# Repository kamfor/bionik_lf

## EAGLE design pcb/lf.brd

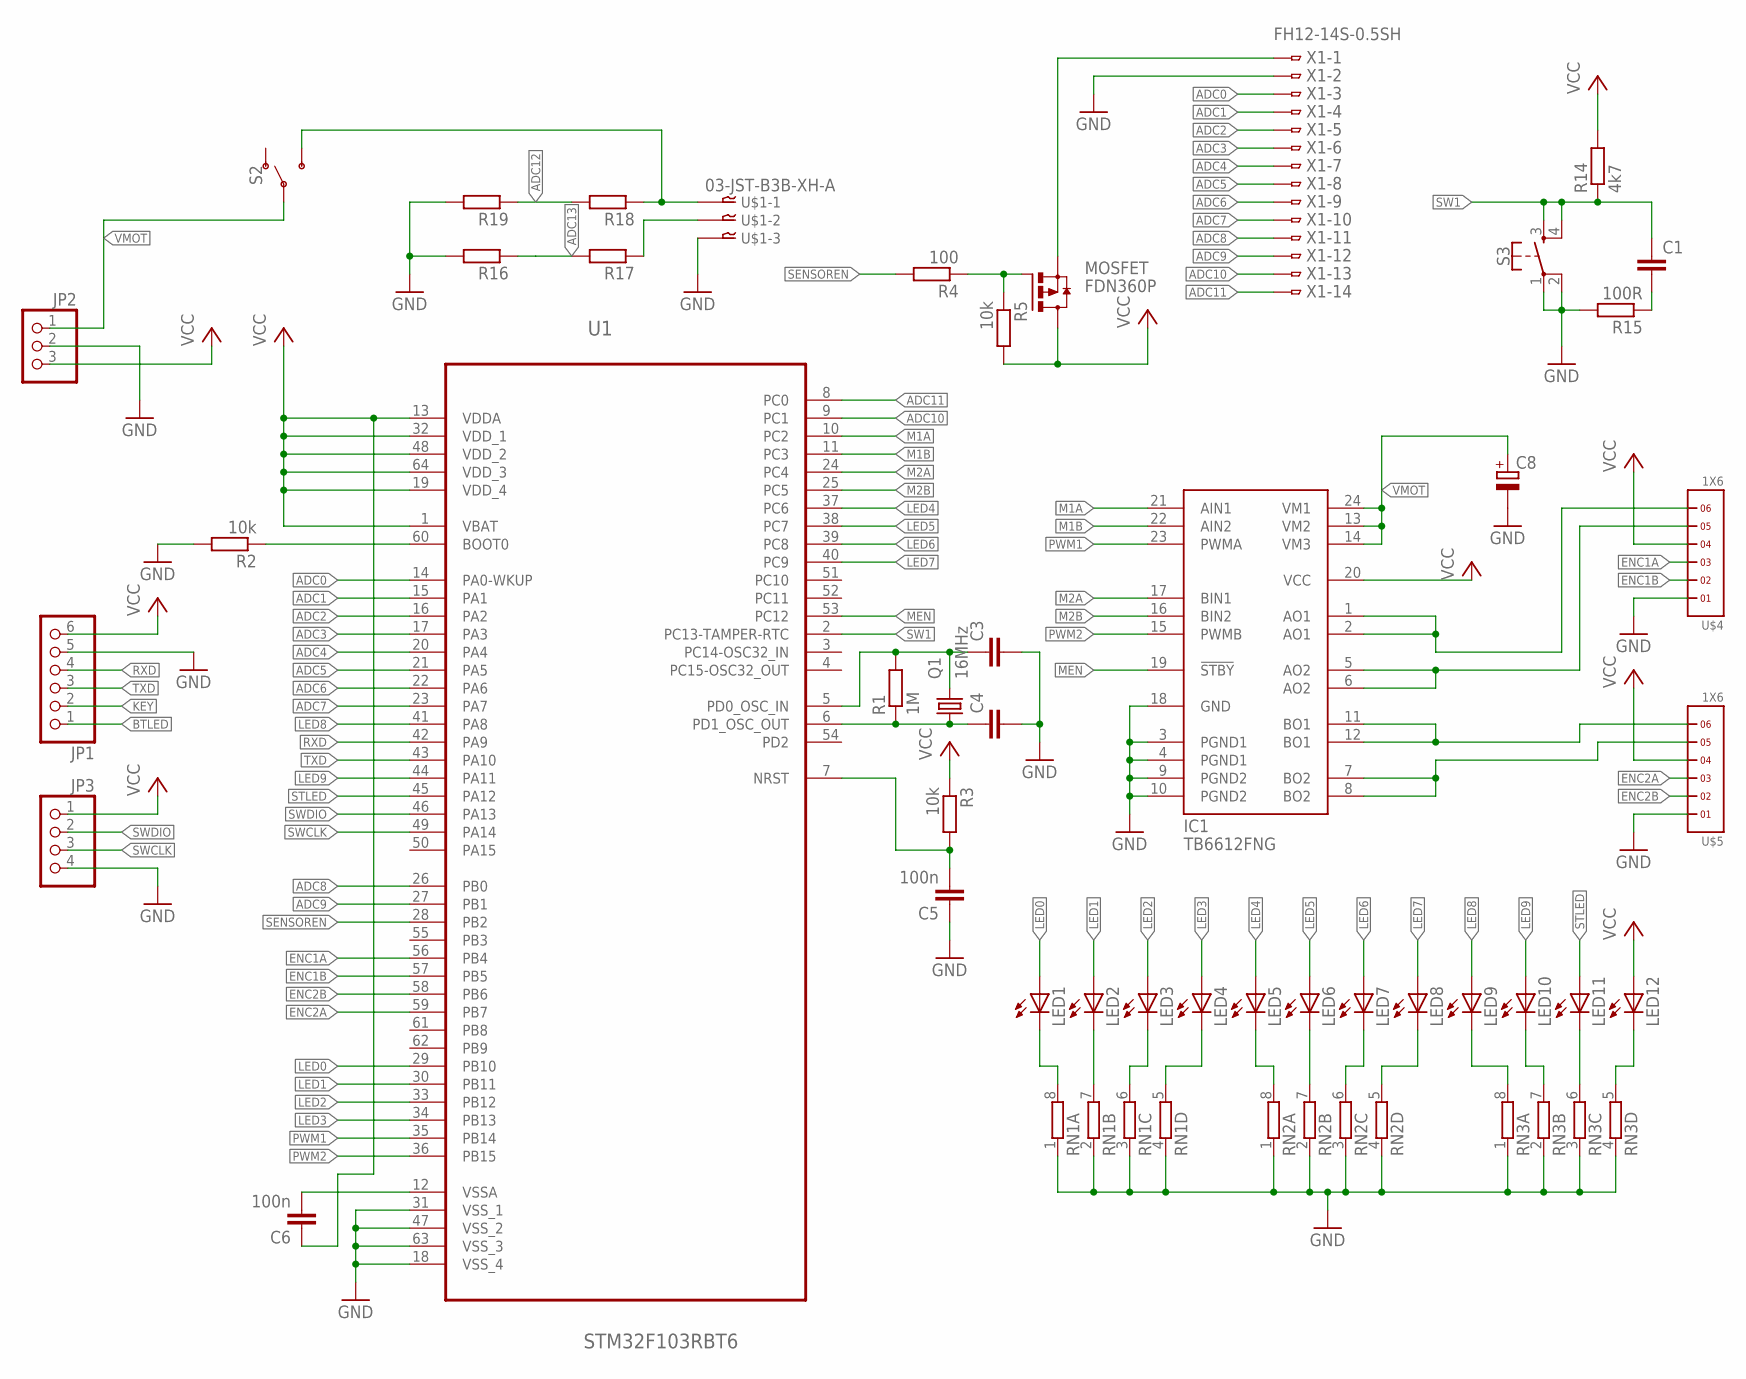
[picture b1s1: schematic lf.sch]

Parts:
C1, C3, C4: C-EUC0603K; C0603K
C5, C6: 100n; C0603K
C8: CPOL-EUC/6032-28R; C/6032-28R
IC1: TB6612FNG; SSOP24
JP1: PINHD-1X6; 1X06
JP2: PINHD-1X3; 1X03
JP3: PINHD-1X4; 1X04
LED1, LED2, LED3, LED4, LED5, LED6, LED7, LED8, LED9, LED10, LED11, LED12: LEDCHIPLED_0603; CHIPLED_0603
MOSFET: FDN360P; SUPER-SOT3
Q1: 16MHz; 3.2X2.5_KX-7
R1: 1M; R0603
R2, R3, R5: 10k; R0603
R4: 100; R0603
R14: 4k7; R0603
R15: 100R; R0603
R16, R17, R18, R19: R-EU_R0603; R0603
RN1, RN2, RN3: 4R-NEXB28V; EXB28V
S2: SWITCH-SPDT-PTH-11.6X4.0MM; SWITCH_SPDT_PTH_11.6X4.0MM
S3: MOMENTARY-SWITCH-SPST-2-SMD-5.2MM; TACTILE_SWITCH_SMD_5.2MM
U1: STM32F103RBT6; QFP50P1200X1200X160-64N
U$1: 03-JST-B3B-XH-A; B3B-XH
U$4, U$5: 1X6
X1: FH12-14S-0.5SH

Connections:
ADC0: U1.14 (PA0-WKUP), X1.3
ADC1: U1.15 (PA1), X1.4
ADC2: U1.16 (PA2), X1.5
ADC3: U1.17 (PA3), X1.6
ADC4: U1.20 (PA4), X1.7
ADC5: U1.21 (PA5), X1.8
ADC6: U1.22 (PA6), X1.9
ADC7: U1.23 (PA7), X1.10
ADC8: U1.26 (PB0), X1.11
ADC9: U1.27 (PB1), X1.12
ADC10: U1.9 (PC1), X1.13
ADC11: U1.8 (PC0), X1.14
ADC12: R18.2, R19.1
ADC13: R16.1, R17.2
BTLED: JP1.1
ENC1A: U1.56 (PB4), U$4.3
ENC1B: U1.57 (PB5), U$4.2
ENC2A: U1.59 (PB7), U$5.3
ENC2B: U1.58 (PB6), U$5.2
GND: C3.2, C4.2, C5.1, C8.-, IC1.3 (PGND1), IC1.4 (PGND1), IC1.9 (PGND2), IC1.10 (PGND2), IC1.18 (GND), JP1.5, JP2.2, JP3.4, R2.2, R15.2, R16.2, R19.2, RN1.1, RN1.2 (1), RN1.3 (1), RN1.4 (1), RN2.1, RN2.2 (1), RN2.3 (1), RN2.4 (1), RN3.1, RN3.2 (1), RN3.3 (1), RN3.4 (1), S3.1, S3.2, U1.18 (VSS_4), U1.31 (VSS_1), U1.47 (VSS_2), U1.63 (VSS_3), U$1.P$3, U$4.1, U$5.1, X1.2
KEY: JP1.2
LED0: LED1.A, U1.29 (PB10)
LED1: LED2.A, U1.30 (PB11)
LED2: LED3.A, U1.33 (PB12)
LED3: LED4.A, U1.34 (PB13)
LED4: LED5.A, U1.37 (PC6)
LED5: LED6.A, U1.38 (PC7)
LED6: LED7.A, U1.39 (PC8)
LED7: LED8.A, U1.40 (PC9)
LED8: LED9.A, U1.41 (PA8)
LED9: LED10.A, U1.44 (PA11)
M1A: IC1.21 (AIN1), U1.10 (PC2)
M1B: IC1.22 (AIN2), U1.11 (PC3)
M2A: IC1.17 (BIN1), U1.24 (PC4)
M2B: IC1.16 (BIN2), U1.25 (PC5)
MEN: IC1.19 (!STBY), U1.53 (PC12)
unnamed: C4.1, Q1.1, R1.1, U1.6 (PD1_OSC_OUT)
unnamed: R2.1, U1.60 (BOOT0)
unnamed: C6.2, U1.12 (VSSA)
unnamed: C1.2, R15.1
unnamed: IC1.5 (AO2), IC1.6 (AO2), U$4.5
unnamed: IC1.11 (BO1), IC1.12 (BO1), U$5.6
unnamed: IC1.7 (BO2), IC1.8 (BO2), U$5.5
unnamed: IC1.1 (AO1), IC1.2 (AO1), U$4.6
unnamed: C3.1, Q1.3 (2), R1.2, U1.5 (PD0_OSC_IN)
unnamed: C5.2, R3.2, U1.7 (NRST)
unnamed: R18.1, S2.3 (S), U$1.P$1
unnamed: R17.1, U$1.P$2
unnamed: LED1.C, RN1.8 (2)
unnamed: LED2.C, RN1.7 (2)
unnamed: LED3.C, RN1.6 (2)
unnamed: LED4.C, RN1.5 (2)
unnamed: LED5.C, RN2.8 (2)
unnamed: LED6.C, RN2.7 (2)
unnamed: LED7.C, RN2.6 (2)
unnamed: LED8.C, RN2.5 (2)
unnamed: LED9.C, RN3.8 (2)
unnamed: LED10.C, RN3.7 (2)
unnamed: LED11.C, RN3.6 (2)
unnamed: LED12.C, RN3.5 (2)
unnamed: MOSFET.1 (G), R4.1, R5.1
unnamed: MOSFET.2 (S), X1.1
PWM1: IC1.23 (PWMA), U1.35 (PB14)
PWM2: IC1.15 (PWMB), U1.36 (PB15)
RXD: JP1.4, U1.42 (PA9)
SENSOREN: R4.2, U1.28 (PB2)
STLED: LED11.A, U1.45 (PA12)
SW1: C1.1, R14.1, S3.3, S3.4, U1.2 (PC13-TAMPER-RTC)
SWCLK: JP3.3, U1.49 (PA14)
SWDIO: JP3.2, U1.46 (PA13)
TXD: JP1.3, U1.43 (PA10)
VCC: C6.1, IC1.20 (VCC), JP1.6, JP2.3, JP3.1, LED12.A, MOSFET.3 (D), R3.1, R5.2, R14.2, U1.1 (VBAT), U1.13 (VDDA), U1.19 (VDD_4), U1.32 (VDD_1), U1.48 (VDD_2), U1.64 (VDD_3), U$4.4, U$5.4
VMOT: C8.+, IC1.13 (VM2), IC1.14 (VM3), IC1.24 (VM1), JP2.1, S2.2

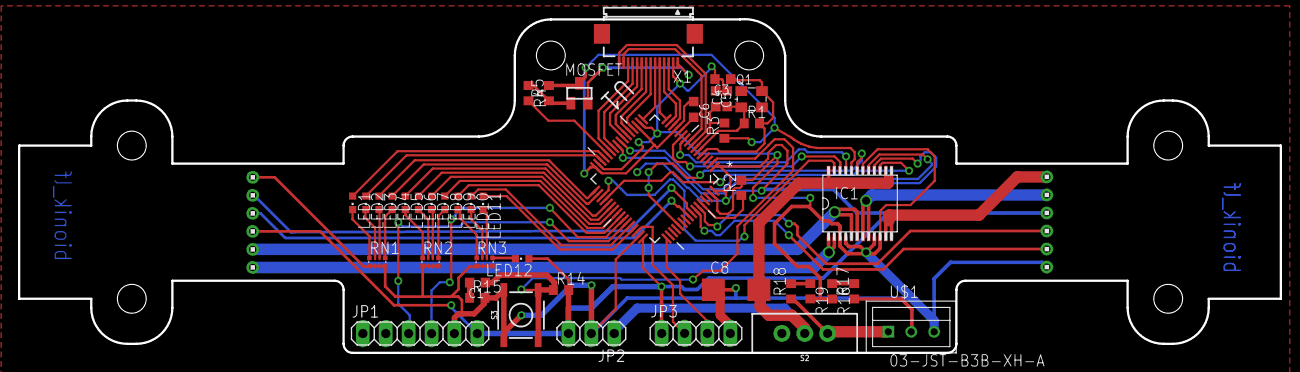
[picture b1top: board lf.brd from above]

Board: 2 copper layers, 140.0 x 37.0 mm, 45 parts (0 on the bottom side), 71 nets.

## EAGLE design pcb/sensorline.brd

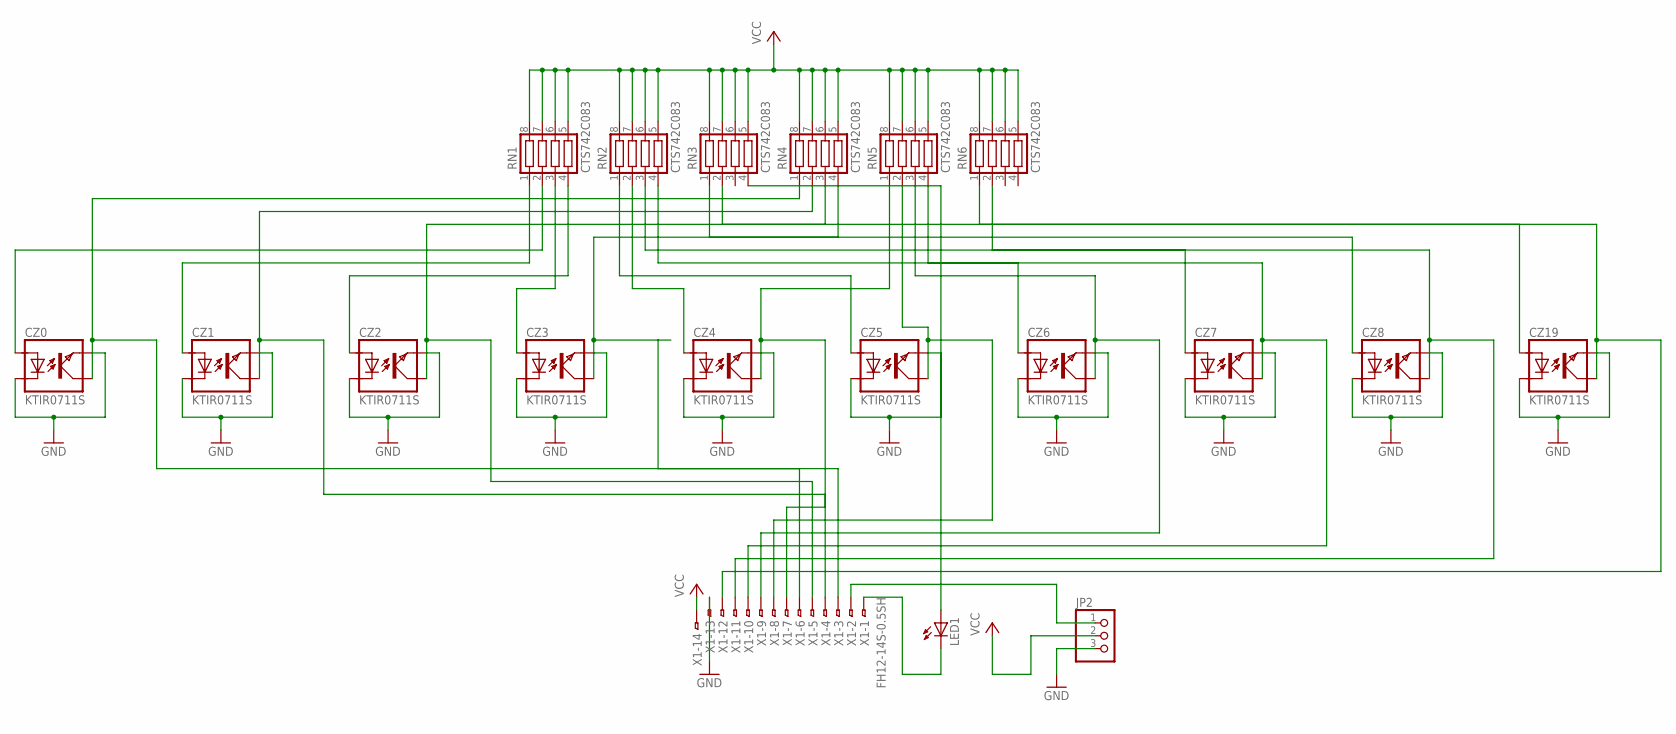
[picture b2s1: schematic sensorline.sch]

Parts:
CZ0, CZ1, CZ2, CZ3, CZ4, CZ5, CZ6, CZ7, CZ8, CZ19: KTIR0711S; TOP
JP2: PINHD-1X3; 1X03
LED1: LEDCHIPLED_0603; CHIPLED_0603
RN1, RN2, RN3, RN4, RN5, RN6: CTS742C083
X1: FH12-14S-0.5SH

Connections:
GND: CZ0.EMITER, CZ0.KATODA, CZ1.EMITER, CZ1.KATODA, CZ2.EMITER, CZ2.KATODA, CZ3.EMITER, CZ3.KATODA, CZ4.EMITER, CZ4.KATODA, CZ5.EMITER, CZ5.KATODA, CZ6.EMITER, CZ6.KATODA, CZ7.EMITER, CZ7.KATODA, CZ8.EMITER, CZ8.KATODA, CZ19.EMITER, CZ19.KATODA, JP2.3, X1.13
unnamed: CZ0.ANODA, RN1.2
unnamed: CZ0.KOLEKTOR, RN4.1, X1.3
unnamed: CZ1.ANODA, RN1.1
unnamed: CZ1.KOLEKTOR, RN4.2, X1.4
unnamed: CZ2.ANODA, RN1.4
unnamed: CZ2.KOLEKTOR, RN4.3, X1.5
unnamed: CZ3.ANODA, RN1.3
unnamed: CZ3.KOLEKTOR, RN4.4, X1.6
unnamed: CZ4.ANODA, RN2.2
unnamed: CZ4.KOLEKTOR, RN5.1, X1.7
unnamed: CZ5.ANODA, RN2.1
unnamed: CZ5.KOLEKTOR, RN5.2, X1.8
unnamed: CZ6.ANODA, RN2.4
unnamed: CZ6.KOLEKTOR, RN5.3, X1.9
unnamed: CZ7.ANODA, RN2.3
unnamed: CZ7.KOLEKTOR, RN5.4, X1.10
unnamed: CZ8.ANODA, RN3.1
unnamed: CZ8.KOLEKTOR, RN6.2, X1.11
unnamed: CZ19.ANODA, RN3.2
unnamed: CZ19.KOLEKTOR, RN6.1, X1.12
unnamed: LED1.A, RN3.4
unnamed: JP2.1, X1.2
unnamed: LED1.C, X1.1
VCC: JP2.2, RN1.5, RN1.6, RN1.7, RN1.8, RN2.5, RN2.6, RN2.7, RN2.8, RN3.5, RN3.6, RN3.7, RN3.8, RN4.5, RN4.6, RN4.7, RN4.8, RN5.5, RN5.6, RN5.7, RN5.8, RN6.5, RN6.6, RN6.7, RN6.8, X1.14

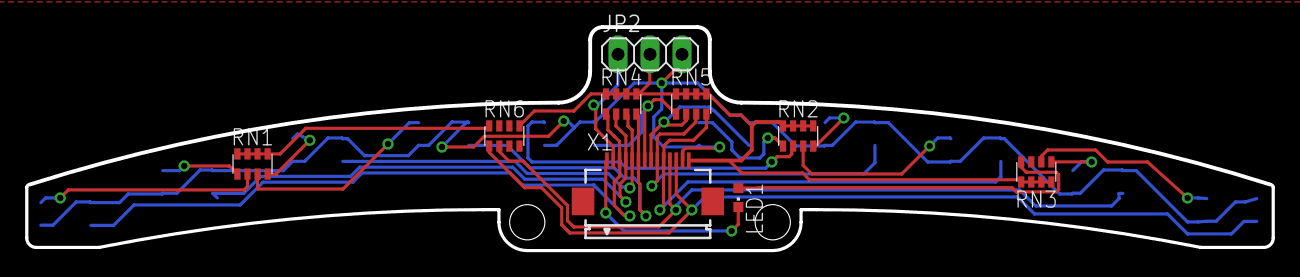
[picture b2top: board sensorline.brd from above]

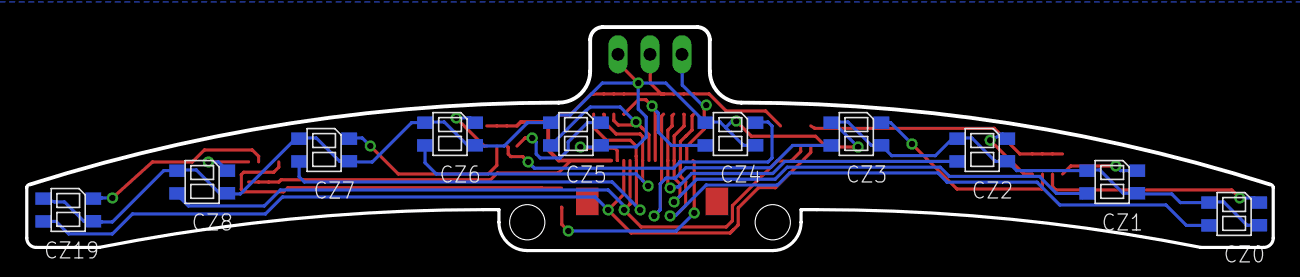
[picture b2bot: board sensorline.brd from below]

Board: 2 copper layers, 98.9 x 17.7 mm, 19 parts (10 on the bottom side), 25 nets.

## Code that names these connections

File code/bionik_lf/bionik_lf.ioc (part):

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Mcu.Name=STM32F103R(8-B)Tx
Mcu.Package=LQFP64
Mcu.UserName=STM32F103RBTx
PA0-WKUP.Signal=ADCx_IN0
PA1.Signal=ADCx_IN1
PA10.Mode=Asynchronous
PA10.Signal=USART1_RX
PA11.GPIOParameters=GPIO_Label
PA11.GPIO_Label=LED9
PA11.Signal=GPIO_Output
PA12.GPIOParameters=GPIO_Label
PA12.GPIO_Label=LED_GREEN
PA12.Signal=GPIO_Output
PA13.Mode=Serial_Wire
PA13.Signal=SYS_JTMS-SWDIO
PA14.Mode=Serial_Wire
PA14.Signal=SYS_JTCK-SWCLK
PA2.Signal=ADCx_IN2
PA3.Signal=ADCx_IN3
PA4.Signal=ADCx_IN4
PA5.Signal=ADCx_IN5
PA6.Signal=ADCx_IN6
PA7.Signal=ADCx_IN7
PA8.GPIOParameters=GPIO_Label
PA8.GPIO_Label=LED8
PA8.Signal=GPIO_Output
PA9.Mode=Asynchronous
PA9.Signal=USART1_TX
PB0.Signal=ADCx_IN8
PB1.Signal=ADCx_IN9
PB10.GPIOParameters=GPIO_Label
PB10.GPIO_Label=LED0
PB10.Signal=GPIO_Output
PB11.GPIOParameters=GPIO_Label
PB11.GPIO_Label=LED1
PB11.Signal=GPIO_Output
PB12.GPIOParameters=GPIO_Label
PB12.GPIO_Label=LED2
PB12.Signal=GPIO_Output
PB13.GPIOParameters=GPIO_Label
PB13.GPIO_Label=LED3
PB13.Signal=GPIO_Output
PB14.GPIOParameters=GPIO_ModeDefaultPP,GPIO_Speed,GPIO_Label
PB14.GPIO_Label=PWM1
PB14.GPIO_ModeDefaultPP=GPIO_MODE_AF_OD
PB14.GPIO_Speed=GPIO_SPEED_FREQ_HIGH
PB14.Mode=PWM Generation2 CH2N
PB14.Signal=TIM1_CH2N
PB15.GPIOParameters=GPIO_Label
PB15.GPIO_Label=PWM2
PB15.Mode=PWM Generation3 CH3N
PB15.Signal=TIM1_CH3N
PB2.GPIOParameters=GPIO_Label
PB2.GPIO_Label=SENSOREN
PB2.Signal=GPIO_Output
PB4.GPIOParameters=GPIO_PuPd
PB4.GPIO_PuPd=GPIO_NOPULL
PB4.Signal=S_TIM3_CH1
PB5.GPIOParameters=GPIO_PuPd
PB5.GPIO_PuPd=GPIO_NOPULL
PB5.Signal=S_TIM3_CH2
PB6.GPIOParameters=GPIO_PuPd
PB6.GPIO_PuPd=GPIO_NOPULL
PB6.Signal=S_TIM4_CH1
PB7.GPIOParameters=GPIO_PuPd
PB7.GPIO_PuPd=GPIO_NOPULL
PB7.Signal=S_TIM4_CH2
PC0.Signal=ADCx_IN10
PC1.Signal=ADCx_IN11
PC12.GPIOParameters=GPIO_Label
PC12.GPIO_Label=MEN
PC12.Signal=GPIO_Output
PC13-TAMPER-RTC.GPIOParameters=GPIO_Label
PC13-TAMPER-RTC.GPIO_Label=SW
PC13-TAMPER-RTC.Signal=GPIO_Input
PC2.GPIOParameters=GPIO_Label
PC2.GPIO_Label=M1A
PC2.Signal=GPIO_Output
PC3.GPIOParameters=GPIO_Label
PC3.GPIO_Label=M1B
PC3.Signal=GPIO_Output
PC4.GPIOParameters=GPIO_Label
PC4.GPIO_Label=M2A
PC4.Signal=GPIO_Output
PC5.GPIOParameters=GPIO_Label
PC5.GPIO_Label=M2B
PC5.Signal=GPIO_Output
PC6.GPIOParameters=GPIO_Label
PC6.GPIO_Label=LED4
PC6.Signal=GPIO_Output
PC7.GPIOParameters=GPIO_Label
PC7.GPIO_Label=LED5
PC7.Signal=GPIO_Output
PC8.GPIOParameters=GPIO_Label
PC8.GPIO_Label=LED6
PC8.Signal=GPIO_Output
PC9.GPIOParameters=GPIO_Label
PC9.GPIO_Label=LED7
PC9.Signal=GPIO_Output
PD0-OSC_IN.Mode=HSE-External-Oscillator
PD0-OSC_IN.Signal=RCC_OSC_IN
PD1-OSC_OUT.Mode=HSE-External-Oscillator
PD1-OSC_OUT.Signal=RCC_OSC_OUT
RCC.HSEDivPLL=RCC_HSE_PREDIV_DIV2
RCC.HSE_VALUE=16000000
RCC.SYSCLKFreq_VALUE=72000000
RCC.SYSCLKSource=RCC_SYSCLKSOURCE_PLLCLK
board=bionik_lf

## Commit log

2017-04-23 initial
2017-05-05 sdsd
2017-05-06 a takie tam poprawki
2017-05-07 schematic complete
2017-05-08 o już niewiele
2017-05-09 hard level
2017-05-10 już końcówka
2017-05-10 done
2017-05-11 gerbery
2017-10-04 part_values
2017-10-26 cubemx
2017-10-26 code core
2017-10-29 adc_test
2017-11-09 jeszcze nic

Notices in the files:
parts and their libraries:
crystal-geyer_V1_0: Copyright: Geyer-Electronic
SparkFun-Switches: Licensing: Creative Commons ShareAlike 4.0 International - https://creativecommons.org/licenses/by-sa/4.0
